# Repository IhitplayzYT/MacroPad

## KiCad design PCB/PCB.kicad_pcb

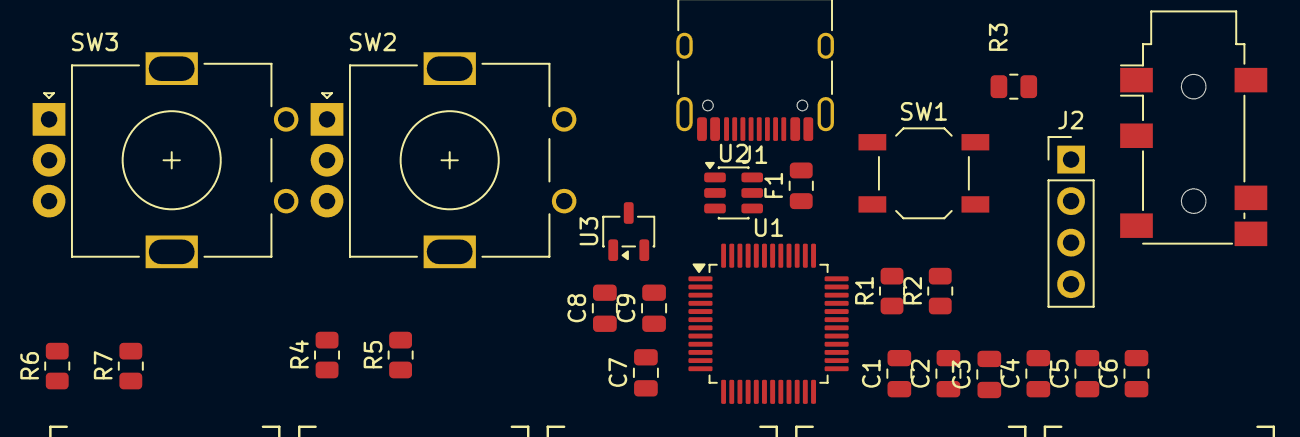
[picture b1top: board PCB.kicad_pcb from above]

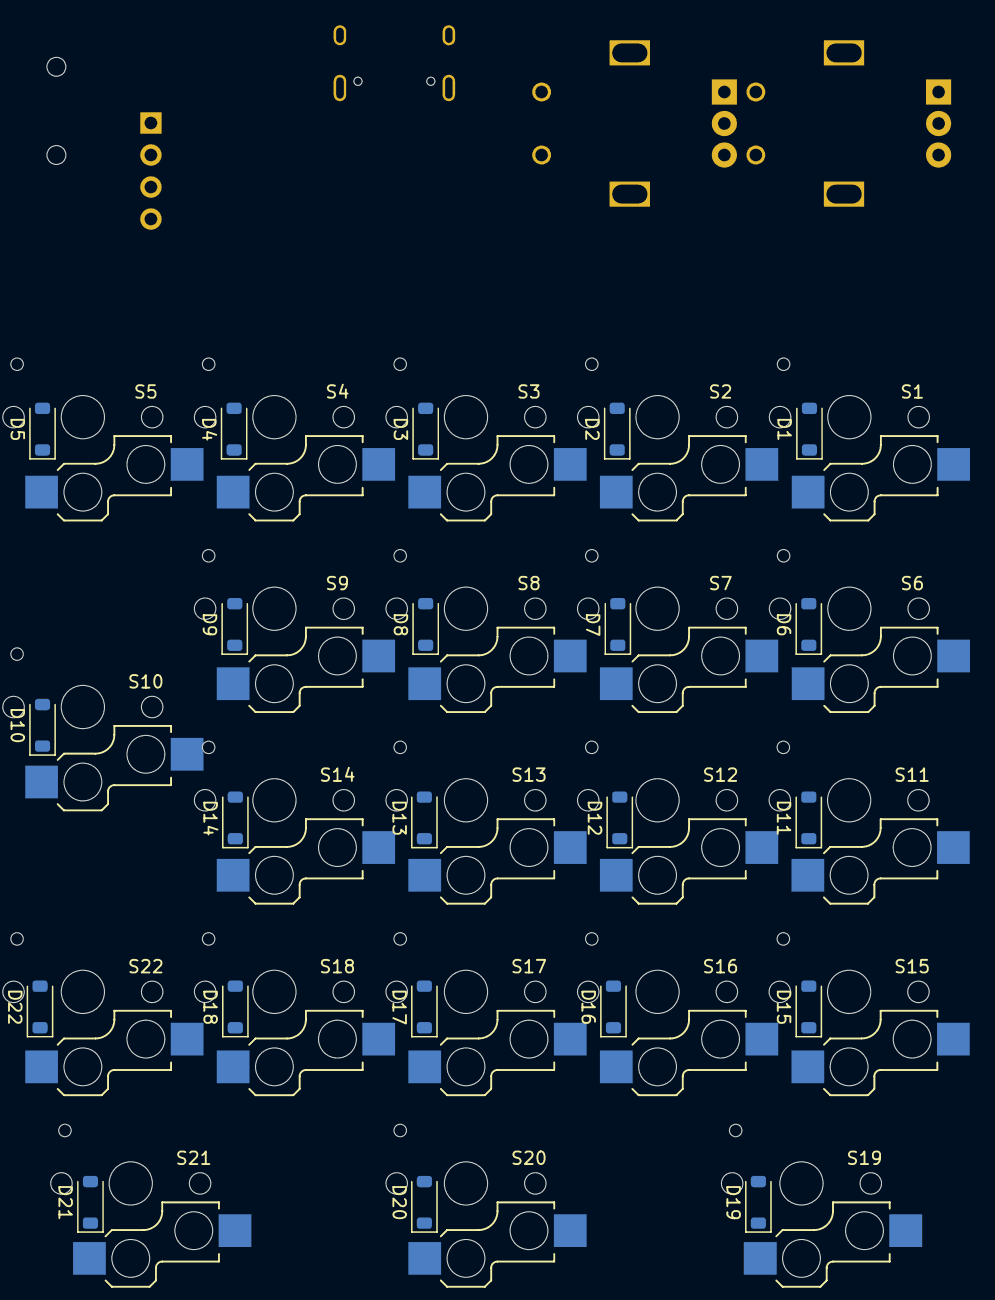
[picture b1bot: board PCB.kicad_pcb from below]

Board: 2 copper layers, 70 parts (22 on the bottom side), 50 nets, no tracks yet.

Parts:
C1, C2, C3, C4, C5, C7: 100nF; C_0805_2012Metric
C6: 10nF; C_0805_2012Metric
C8, C9: 1uF; C_0805_2012Metric
D1, D2, D3, D4, D5, D6, D7, D8, D9, D10, D11, D12, D13, D14, D15, D16, D17, D18, D19, D20, D21, D22: D_SOD-123
F1: 500mA; Fuse_0805_2012Metric
J1: USB_C_Receptacle_USB2.0_14P; USB_C_Receptacle_HRO_TYPE-C-31-M-12
J2: OLED_128x64; PinHeader_1x04_P2.54mm_Vertical
R1, R2: 5.1k; R_0805_2012Metric
R3, R4, R5, R6, R7: 10k; R_0805_2012Metric
S1, S2, S3, S4, S5, S6, S7, S8, S9, S10, S11, S12, S13, S14, S15, S16, S17, S18, S19, S20, S21, S22: Kailh_socket_PG1350
SW1: SW_Push; SW_SPST_TL3342
SW2, SW3: RotaryEncoder; RotaryEncoder_Alps_EC11E_Vertical_H20mm
U1: STM32F072CBTx; LQFP-48_7x7mm_P0.5mm
U2: USBLC6-2SC6; SOT-23-6
U3: XC6206; SOT-23-3
U5: TRRS; Jack_3.5mm_PJ311_Horizontal

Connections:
+3.3V: C1.1, C2.1, C3.1, C4.1, C5.1, C6.1, C9.1, J2.2 (VCC), R4.1, R5.2, R6.1, R7.1, SW1.1, U1.1 (VBAT), U1.9 (VDDA), U1.24 (VDD), U1.36 (VDDIO2), U1.48 (VDD), U3.2 (VO), U5.2 (TIP)
+5V: C8.1, F1.2, U2.5 (VBUS), U3.3 (VI)
BOOT: R3.1, SW1.2, U1.44 (BOOT0)
C0: S1.1, S6.1, S11.1, S15.1, S19.1, U1.45 (PB8)
C1: S2.1, S7.1, S12.1, S16.1, S20.1, U1.46 (PB9)
C2: S3.1, S8.1, S13.1, S17.1, S21.1, U1.21 (PB10)
C3: S4.1, S9.1, S14.1, S18.1, U1.22 (PB11)
C4: S5.1, S10.1, S22.1, U1.25 (PB12)
D+: J1.A6 (D+), J1.B6 (D+), U1.33 (PA12), U2.1 (I/O1), U2.6 (I/O1)
D-: J1.A7 (D-), J1.B7 (D-), U1.32 (PA11), U2.3 (I/O2), U2.4 (I/O2)
GND: C1.2, C2.2, C3.2, C4.2, C5.2, C6.2, C7.1, C8.2, C9.2, J1.A1 (GND), J1.A12 (GND), J1.B1 (GND), J1.B12 (GND), J1.SH (SHIELD), J2.1 (GND), R1.2, R2.2, R3.2, SW2.C, SW3.C, U1.8 (VSSA), U1.23 (VSS), U1.35 (VSS), U1.47 (VSS), U2.2 (GND), U3.1 (GND), U5.3 (RING1)
unnamed: D1.2 (A), S1.2
unnamed: D2.2 (A), S2.2
unnamed: D3.2 (A), S3.2
unnamed: D4.2 (A), S4.2
unnamed: D5.2 (A), S5.2
unnamed: D6.2 (A), S6.2
unnamed: D7.2 (A), S7.2
unnamed: D8.2 (A), S8.2
unnamed: D9.2 (A), S9.2
unnamed: D10.2 (A), S10.2
unnamed: D11.2 (A), S11.2
unnamed: D12.2 (A), S12.2
unnamed: D13.2 (A), S13.2
unnamed: D14.2 (A), S14.2
unnamed: D15.2 (A), S15.2
unnamed: D16.2 (A), S16.2
unnamed: D17.2 (A), S17.2
unnamed: D18.2 (A), S18.2
unnamed: D19.2 (A), S19.2
unnamed: D20.2 (A), S20.2
unnamed: D21.2 (A), S21.2
unnamed: D22.2 (A), S22.2
unnamed: J1.A5 (CC1), R1.1
unnamed: J1.B5 (CC2), R2.1
unnamed: C7.2, U1.7 (NRST)
R0: D1.1 (K), D2.1 (K), D3.1 (K), D4.1 (K), D5.1 (K), U1.18 (PB0)
R1: D6.1 (K), D7.1 (K), D8.1 (K), D9.1 (K), D10.1 (K), U1.19 (PB1)
R2: D11.1 (K), D12.1 (K), D13.1 (K), D14.1 (K), U1.20 (PB2)
R3: D15.1 (K), D16.1 (K), D17.1 (K), D18.1 (K), D22.1 (K), U1.39 (PB3)
R4: D19.1 (K), D20.1 (K), D21.1 (K), U1.40 (PB4)
RE_1_A: R5.1, SW2.B, U1.10 (PA0)
RE_1_B: R4.2, SW2.A, U1.11 (PA1), U1.12 (PA2)
RE_2_A: R6.2, SW3.B, U1.17 (PA7)
RE_2_B: R7.2, SW3.A, U1.29 (PA8)
RX: U1.31 (PA10), U5.4 (RING2)
SCL: J2.3 (SCL), U1.42 (PB6)
SDA: J2.4 (SDA), U1.43 (PB7)
TX: U1.30 (PA9), U5.1 (SLEEVE)
VBUS: F1.1, J1.A4 (VBUS), J1.A9 (VBUS), J1.B4 (VBUS), J1.B9 (VBUS)

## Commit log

2026-04-14 A intermediate project before i move forward with main split keyboard project
2026-04-15 Started trying to route the traces
2026-04-15 Added rotatry knobs to sketch
2026-04-16 Done with the kiCad Matrix layout placement in sketch
2026-04-16 Finally done orchestrating and placing of component on PCB
2026-04-17 GGs finally fucking finished routing the retardly dense clustered traces now i understand why em electronic board based prods so expensive gng
2026-04-17 Finally DCR check passed
2026-04-19 Updated the PCB with proper alignments and design decisions
2026-04-22 Improved routing and the first final iteration of PCB
2026-05-01 Added sd card and fixed some wirings
